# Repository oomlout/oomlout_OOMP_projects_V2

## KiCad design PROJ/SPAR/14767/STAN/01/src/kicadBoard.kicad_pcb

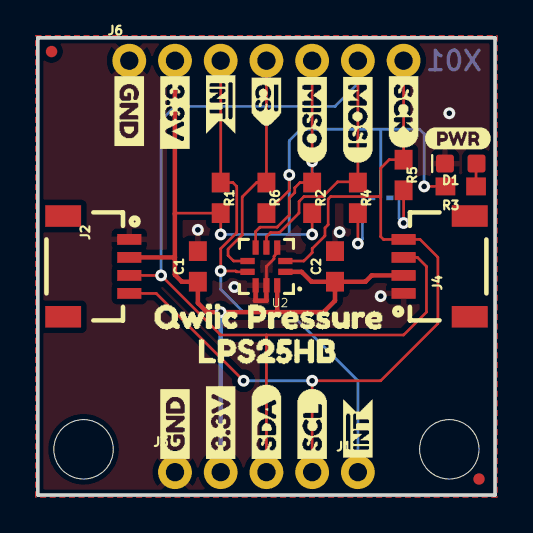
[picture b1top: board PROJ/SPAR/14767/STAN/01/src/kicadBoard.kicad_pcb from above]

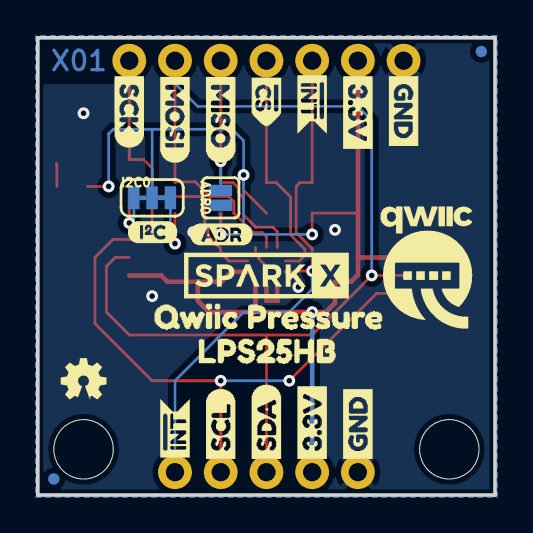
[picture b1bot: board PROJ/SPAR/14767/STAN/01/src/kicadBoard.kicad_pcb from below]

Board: 2 copper layers, 25.4 x 25.4 mm, 58 parts (23 on the bottom side), 10 nets.

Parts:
ADR0: SMT-JUMPER_2_NO_SILK
C1: 4.7uF; 0603
C2: 0.1uF; 0603
D1: RED; LED-0603
FRAME1: FRAME-LETTER; CREATIVE_COMMONS
I2C0: SMT-JUMPER_3_2-NC_TRACE_SILK
J1: 1X01_NO_SILK
J2, J4: 1X04_1MM_RA
J3: PTH; 1X04_NO_SILK
J6: 1X07_NO_SILK
JP1, JP2, JP5, JP6: FIDUCIALUFIDUCIAL; MICRO-FIDUCIAL
JP3, JP4: STAND-OFF
LOGO1: OSHW-LOGOMINI; OSHW-LOGO-MINI
R1, R2, R6: 10k; 0603
R3: 1k; 0603
R4, R5: 2.2k; 0603
U2: LPS25HB
U$1, U$37: QWIIC_PRESSURE1
U$2: SPARKX-LOGO4; SPARKX-MEDIUM
U$3, U$22, U$31, U$32: GND1
U$4, U$21, U$30, U$33: 3#3V2
U$5, U$27: SDA8
U$6, U$26: SCL9
U$7, U$35: LPS25HB0
U$9: QWIIC-LOGO-MEDIUM
U$10, U$11: MISO
U$12: I_SUPER2_C-()-03
U$15: PWR-()-03
U$16, U$17: MOSI
U$18, U$19: SCK-[)
U$20, U$23: CS#-[_
U$24, U$25, U$28, U$29: INT#-[_
U$34: ADR-()-03

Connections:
3.3V: C1.1, C2.1, I2C0.2, J2.2, J3.2, J4.2, J6.2, R1.2, R2.2, R3.2, R6.2, U2.1, U2.10
ADDR/MISO: ADR0.2, J6.5, R2.1, U2.5
CS: J6.4, R6.1, U2.6
GND: ADR0.1, C1.2, C2.2, D1.C, J2.1, J3.1, J4.1, J6.1, U2.3, U2.8, U2.9
unnamed: I2C0.1, R5.2
unnamed: I2C0.3, R4.2
unnamed: D1.A, R3.1
SCL/SCK: J2.4, J3.4, J4.4, J6.7, R5.1, U2.2
SDA/MOSI: J2.3, J3.3, J4.3, J6.6, R4.1, U2.4
~INT: J1.1, J6.3, R1.1, U2.7

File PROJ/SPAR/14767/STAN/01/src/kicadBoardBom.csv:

"Id";"Designator";"Package";"Quantity";"Designation";"Supplier and ref";
1;"U$28,U$24,U$25,U$29";"INT#-[_";4;"";;;
2;"C1";"0603";1;"4.7uF";;;
3;"U$37,U$1";"QWIIC_PRESSURE1";2;"";;;
4;"U$17,U$16";"MOSI";2;"";;;
5;"U$35,U$7";"LPS25HB0";2;"";;;
6;"U$31,U$22,U$32,U$3";"GND1";4;"";;;
7;"U$26,U$6";"SCL9";2;"";;;
8;"D1";"LED-0603";1;"RED";;;
9;"JP3,JP4";"STAND-OFF";2;"STAND-OFF";;;
10;"R3";"0603";1;"1k";;;
11;"JP2,JP6,JP1,JP5";"MICRO-FIDUCIAL";4;"FIDUCIALUFIDUCIAL";;;
12;"R1,R6,R2";"0603";3;"10k";;;
13;"R4,R5";"0603";2;"2.2k";;;
14;"U$18,U$19";"SCK-[)";2;"";;;
15;"J4,J2";"1X04_1MM_RA";2;"";;;
16;"U$10,U$11";"MISO";2;"";;;
17;"U$15";"PWR-()-03";1;"";;;
18;"C2";"0603";1;"0.1uF";;;
19;"U$30,U$21,U$4,U$33";"3#3V2";4;"";;;
20;"U$20,U$23";"CS#-[_";2;"";;;
21;"U$27,U$5";"SDA8";2;"";;;
22;"J6";"1X07_NO_SILK";1;"";;;
23;"U2";"LPS25HB";1;"LPS25HB";;;
24;"FRAME1";"CREATIVE_COMMONS";1;"FRAME-LETTER";;;
25;"J3";"1X04_NO_SILK";1;"PTH";;;
26;"J1";"1X01_NO_SILK";1;"";;;
27;"U$9";"QWIIC-LOGO-MEDIUM";1;"";;;
28;"U$34";"ADR-()-03";1;"";;;
29;"ADR0";"SMT-JUMPER_2_NO_SILK";1;"";;;
30;"I2C0";"SMT-JUMPER_3_2-NC_TRACE_SILK";1;"";;;
31;"U$12";"I_SUPER2_C-()-03";1;"";;;
32;"LOGO1";"OSHW-LOGO-MINI";1;"OSHW-LOGOMINI";;;
33;"U$2";"SPARKX-MEDIUM";1;"SPARKX-LOGO4";;;

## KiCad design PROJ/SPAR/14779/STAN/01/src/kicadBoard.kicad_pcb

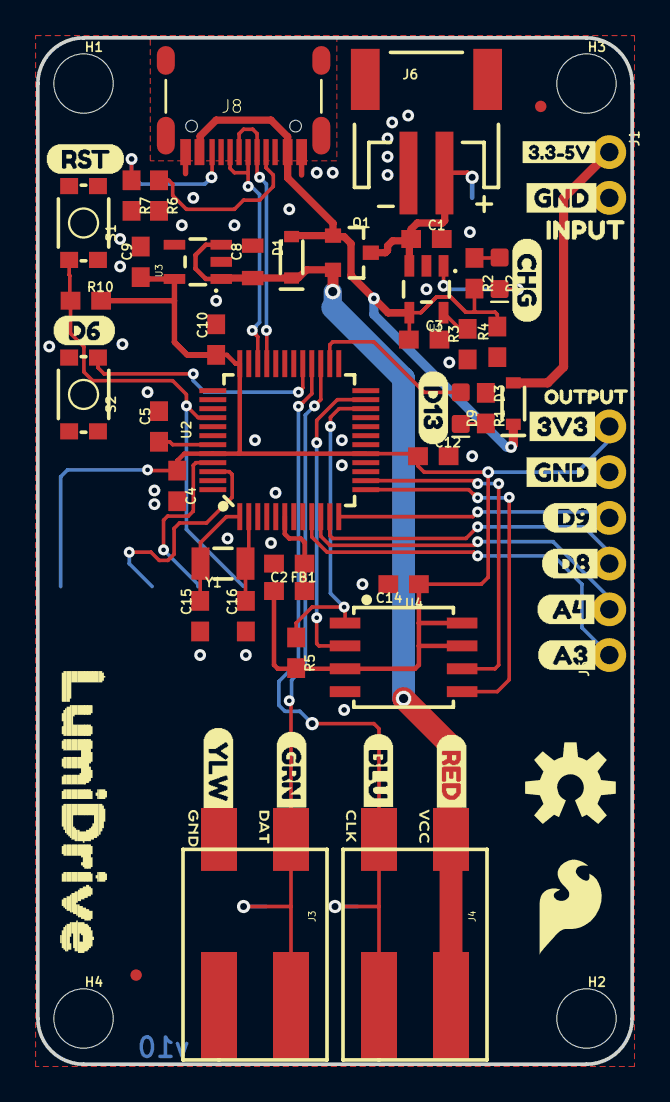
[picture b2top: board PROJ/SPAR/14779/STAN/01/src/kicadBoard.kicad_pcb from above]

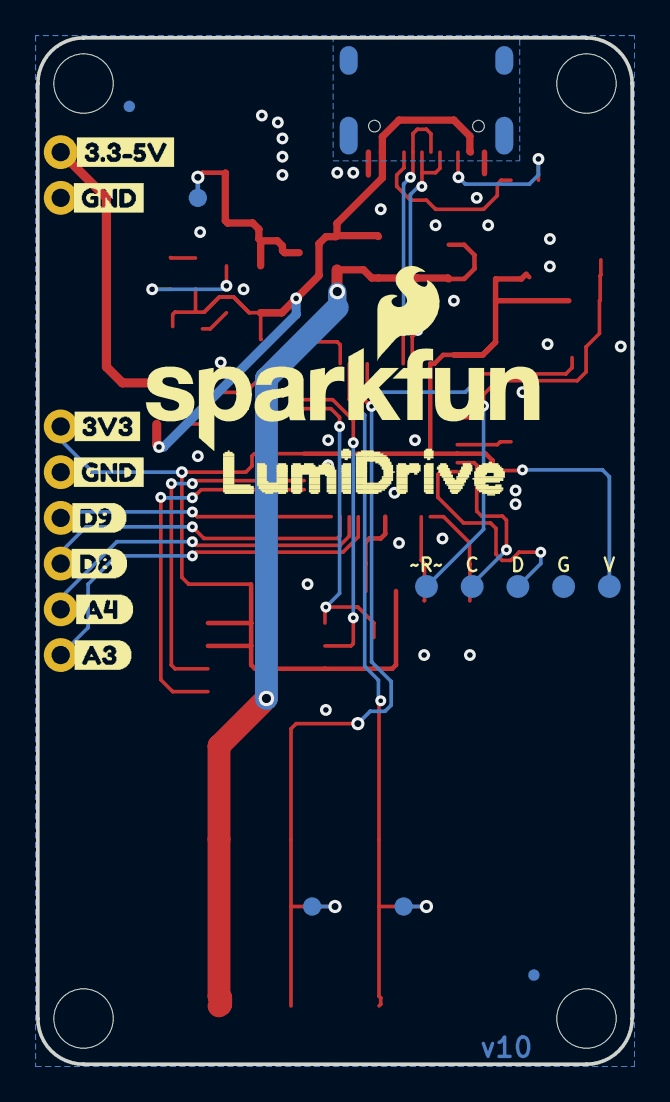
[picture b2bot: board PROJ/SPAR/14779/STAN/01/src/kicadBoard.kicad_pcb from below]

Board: 4 copper layers, 33.0 x 57.0 mm, 91 parts (20 on the bottom side), 34 nets.

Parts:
C1, C3: 4.7uF; 0603
C2, C4, C5, C10, C12, C14: 0.1uF; 0603
C8: 1.0uF; 0805
C9: 2.2uF; 0603
C15, C16: 15pF; 0603
D1, D3: 1A/23V/620mV; SOD-323
D2: Yellow; LED-0603
D9: BLUE; LED-0603
FB1: 30Ω/1.8A; 0603
FD1, FD2, FD3, FD4: FIDUCIALUFIDUCIAL; FIDUCIAL-MICRO
FRAME1: FRAME-LETTER; CREATIVE_COMMONS
H1, H2, H3, H4: STAND-OFF
J1: 1X02_NO_SILK
J3, J4: 1X02_POKEHOME
J5: 1X06_NO_SILK
J6: JST-2-SMD
J8: USB-C-16P
LOGO1: OSHW-LOGOM; OSHW-LOGO-M
LOGO3: SFE_LOGO_NAME_FLAME.2_INCH; SFE_LOGO_NAME_FLAME_.2
Q1: 2.5A/30V/105mΩ; SOT23-3
R1, R2: 1k; 0603
R3: 2.0k; 0603
R4, R5, R10: 10k; 0603
R6, R7: 5.1k; 0603
S1: RESET; TACTILE_SWITCH_SMD_4.6X2.8MM
S2: BTN2; TACTILE_SWITCH_SMD_4.6X2.8MM
TP1: TP-SWDIO; PAD.03X.05
TP2: TP-SWCLK; PAD.03X.05
TP3: TP-!RESET!; PAD.03X.05
TP4: TP-3.3V; PAD.03X.05
TP5: TP-GND; PAD.03X.05
TP6, TP7, TP8: TEST-POINT3X4; PAD.03X.04
U1: MCP73831; SOT23-5
U2: ATSAMD21G-A; TQFP-48
U3: 3.3V; SOT23-5
U4: W25Q32FV; SOIC-8
U$1, U$5, U$19, U$26: GND-04
U$2: GRN0
U$3: BLU0
U$4: YLW0
U$6, U$41: LUMIDRIVE0
U$8, U$29: 3#3#5V0
U$9: INPUT0
U$10: RED0
U$11: RST0
U$12: D60
U$13: CLK1
U$14: DAT2
U$15: GND0
U$16: VCC3
U$17: CHG0
U$18: D130
U$20, U$27: 3V3-04
U$21, U$40: D90
U$22, U$39: D80
U$23, U$38: A40
U$24, U$37: A30
U$25: OUTPUT0
U$28: SFE_LOGO_FLAME_.2
Y1: 32.768kHz; CRYSTAL-SMD-3.2X1.5MM

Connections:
3.3V: C4.1, C9.1, C10.1, C12.1, C14.1, FB1.1, J5.6, R5.2, R10.2, TP4.P$1, U2.17, U2.36, U2.44, U3.5, U4.3, U4.7, U4.8
5V: D3.A, J1.1
A3: J5.1, U2.9
A4: J5.2, U2.10
D6_BTN: S2.4, U2.29
D8: J5.3, U2.11
D9: J5.4, U2.12
D13_LED1: D9.A, U2.26
FLASH_CS: R5.1, U2.22, U4.1
GND: C1.2, C2.2, C3.2, C4.2, C5.2, C8.2, C9.2, C10.2, C12.2, C14.2, C15.1, C16.1, J1.2, J3.P1, J3.P3, J5.5, J6.1, J8.GND, J8.GND2, R1.1, R3.1, R4.1, R6.2, R7.2, S1.3, S2.1, TP5.P$1, U1.2, U2.5, U2.18, U2.35, U2.42, U3.2, U4.4
LED_MOSI: J3.P2, J3.P4, TP7.P$1, U2.27
LED_SCK: J4.P1, J4.P3, TP8.P$1, U2.28
unnamed: D9.C, R1.2
unnamed: C15.2, U2.1, Y1.P$2
unnamed: C16.2, U2.2, Y1.P$1
unnamed: D2.A, R2.1
unnamed: J8.B5, R7.1
unnamed: J8.A5, R6.1
unnamed: D2.C, U1.1
unnamed: R3.2, U1.5
SHIELD: J8.SHLD1, J8.SHLD2, J8.SHLD3, J8.SHLD4, J8.SHLD5, J8.SHLD6, J8.SHLD7, J8.SHLD8
SPI_MISO: U2.23, U4.2
SPI_MOSI: U2.13, U4.5
SPI_SCK: U2.14, U4.6
SWCLK: TP2.P$1, U2.45
SWDIO: TP1.P$1, U2.46
USB_D+: J8.A6, J8.B6, U2.34
USB_D-: J8.A7, J8.B7, U2.33
VDDANA: C2.1, FB1.2, U2.6
VDDCORE: C5.1, U2.43
VIN: C8.1, D1.C, J4.P2, J4.P4, Q1.2, U3.1, U3.3
V_BATT: C1.1, J6.2, Q1.3, TP6.P$1, U1.3
V_USB: C3.1, D1.A, D3.C, J8.VBUS1, J8.VBUS2, Q1.1, R2.2, R4.2, U1.4
~RESET: R10.1, S1.2, TP3.P$1, U2.40

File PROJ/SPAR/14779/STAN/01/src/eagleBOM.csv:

"Part";"Value";"Device";"Package";"Description";"DESIGNER";"PROD_ID";"REV";"SF_ID";"VALUE";
"C1";"4.7uF";"4.7UF-0603-6.3V-(10%)";"0603";"4.7µF ceramic capacitors";"";"CAP-08280";"";"";"4.7uF";
"C2";"0.1uF";"0.1UF-0603-25V-(+80/-20%)";"0603";"0.1µF ceramic capacitors";"";"CAP-00810";"";"";"0.1uF";
"C3";"4.7uF";"4.7UF-0603-6.3V-(10%)";"0603";"4.7µF ceramic capacitors";"";"CAP-08280";"";"";"4.7uF";
"C4";"0.1uF";"0.1UF-0603-25V-(+80/-20%)";"0603";"0.1µF ceramic capacitors";"";"CAP-00810";"";"";"0.1uF";
"C5";"0.1uF";"0.1UF-0603-25V-(+80/-20%)";"0603";"0.1µF ceramic capacitors";"";"CAP-00810";"";"";"0.1uF";
"C8";"1.0uF";"1.0UF-0805-25V-10%";"0805";"1µF ceramic capacitors";"";"CAP-08064";"";"";"1.0uF";
"C9";"2.2uF";"2.2UF-0603-10V-20%";"0603";"2.2µF ceramic capacitors";"";"CAP-07888";"";"";"2.2uF";
"C10";"0.1uF";"0.1UF-0603-25V-(+80/-20%)";"0603";"0.1µF ceramic capacitors";"";"CAP-00810";"";"";"0.1uF";
"C12";"0.1uF";"0.1UF-0603-25V-(+80/-20%)";"0603";"0.1µF ceramic capacitors";"";"CAP-00810";"";"";"0.1uF";
"C14";"0.1uF";"0.1UF-0603-25V-(+80/-20%)";"0603";"0.1µF ceramic capacitors";"";"CAP-00810";"";"";"0.1uF";
"C15";"15pF";"15PF-0603-50V-5%";"0603";"15pF ceramic capacitors";"";"CAP-07881";"";"";"15pF";
"C16";"15pF";"15PF-0603-50V-5%";"0603";"15pF ceramic capacitors";"";"CAP-07881";"";"";"15pF";
"D1";"1A/23V/620mV";"DIODE-SCHOTTKY-BAT20J";"SOD-323";"Schottky diode";"";"DIO-11623";"";"";"1A/23V/620mV";
"D2";"Yellow";"LED-YELLOW0603";"LED-0603";"Yellow SMD LED";"";"DIO-09003";"";"";"Yellow";
"D3";"1A/23V/620mV";"DIODE-SCHOTTKY-BAT20J";"SOD-323";"Schottky diode";"";"DIO-11623";"";"";"1A/23V/620mV";
"D9";"BLUE";"LED-BLUE0603";"LED-0603";"Blue SMD LED";"";"DIO-08575";"";"";"BLUE";
"FB1";"30Ω/1.8A";"INDUCTORFB-30OHM";"0603";"Inductors";"";"NDUC-07859";"";"";"";
"FD1";"FIDUCIALUFIDUCIAL";"FIDUCIALUFIDUCIAL";"FIDUCIAL-MICRO";"Fiducial Alignment Points";"";"";"";"";"";
"FD2";"FIDUCIALUFIDUCIAL";"FIDUCIALUFIDUCIAL";"FIDUCIAL-MICRO";"Fiducial Alignment Points";"";"";"";"";"";
"FD3";"FIDUCIALUFIDUCIAL";"FIDUCIALUFIDUCIAL";"FIDUCIAL-MICRO";"Fiducial Alignment Points";"";"";"";"";"";
"FD4";"FIDUCIALUFIDUCIAL";"FIDUCIALUFIDUCIAL";"FIDUCIAL-MICRO";"Fiducial Alignment Points";"";"";"";"";"";
"FRAME1";"FRAME-LETTER";"FRAME-LETTER";"CREATIVE_COMMONS";"Schematic Frame - Letter";"";"";"";"";"";
"H1";"STAND-OFF";"STAND-OFF";"STAND-OFF";"Stand Off";"";"";"";"";"";
"H2";"STAND-OFF";"STAND-OFF";"STAND-OFF";"Stand Off";"";"";"";"";"";
"H3";"STAND-OFF";"STAND-OFF";"STAND-OFF";"Stand Off";"";"";"";"";"";
"H4";"STAND-OFF";"STAND-OFF";"STAND-OFF";"Stand Off";"";"";"";"";"";
"J1";"";"CONN_021X02_NO_SILK";"1X02_NO_SILK";"Multi connection point. Often used as Generic Header-pin footprint for 0.1 inch spaced/style header connections";"";"";"";"";"";
"J3";"";"CONN_02SMALL_POKEHOME";"1X02_POKEHOME";"Multi connection point. Often used as Generic Header-pin footprint for 0.1 inch spaced/style header connections";"";"CONN-13512";"";"";"";
"J4";"";"CONN_02SMALL_POKEHOME";"1X02_POKEHOME";"Multi connection point. Often used as Generic Header-pin footprint for 0.1 inch spaced/style header connections";"";"CONN-13512";"";"";"";
"J5";"";"CONN_06NO_SILK_FEMALE_PTH";"1X06_NO_SILK";"Multi connection point. Often used as Generic Header-pin footprint for 0.1 inch spaced/style header connections";"";"CONN-08437";"";"";"";
"J6";"";"JST_2MM_MALE";"JST-2-SMD";"JST 2MM MALE RA CONNECTOR";"";"CONN-11443";"";"PRT-08612";"";
"J8";"";"USB_C16PIN";"USB-C-16P";"USB Type C 16Pin Connector";"";"CONN-14122";"";"";"";
"LOGO1";"OSHW-LOGOM";"OSHW-LOGOM";"OSHW-LOGO-M";"Open-Source Hardware (OSHW) Logo";"";"";"";"";"";
"LOGO3";"SFE_LOGO_NAME_FLAME.2_INCH";"SFE_LOGO_NAME_FLAME.2_INCH";"SFE_LOGO_NAME_FLAME_.2";"SparkFun Font Logo w/ Flame";"";"";"";"";"";
"Q1";"2.5A/30V/105mΩ";"MOSFET_PCH-DMG2307L";"SOT23-3";"P-channel MOSFETs";"";"TRANS-11308";"";"";"2.5A/30V/105mΩ";
"R1";"1k";"1KOHM-0603-1/10W-1%";"0603";"1kΩ resistor";"";"RES-07856";"";"";"1k";
"R2";"1k";"1KOHM-0603-1/10W-1%";"0603";"1kΩ resistor";"";"RES-07856";"";"";"1k";
"R3";"2.0k";"2.0KOHM-0603-1/10W-5%";"0603";"2kΩ resistor";"";"RES-08296";"";"";"2.0k";
"R4";"10k";"10KOHM-0603-1/10W-1%";"0603";"10kΩ resistor";"";"RES-00824";"";"";"10k";
"R5";"10k";"10KOHM-0603-1/10W-1%";"0603";"10kΩ resistor";"";"RES-00824";"";"";"10k";
"R6";"5.1k";"5.1KOHM5.1KOHM-0603-1/10W-1%";"0603";"";"";"RES-12083";"";"";"5.1k";
"R7";"5.1k";"5.1KOHM5.1KOHM-0603-1/10W-1%";"0603";"";"";"RES-12083";"";"";"5.1k";
"R10";"10k";"10KOHM-0603-1/10W-1%";"0603";"10kΩ resistor";"";"RES-00824";"";"";"10k";
"S1";"RESET";"MOMENTARY-SWITCH-SPST-2-SMD-4.6X2.8MM";"TACTILE_SWITCH_SMD_4.6X2.8MM";"Momentary Switch (Pushbutton) - SPST - Two Circuits";"";"SWCH-13065";"";"";"";
"S2";"BTN2";"MOMENTARY-SWITCH-SPST-2-SMD-4.6X2.8MM";"TACTILE_SWITCH_SMD_4.6X2.8MM";"Momentary Switch (Pushbutton) - SPST - Two Circuits";"";"SWCH-13065";"";"";"";
"TP1";"TP-SWDIO";"TEST-POINT3X5";"PAD.03X.05";"SparkFun Test Points";"";"";"";"";"";
"TP2";"TP-SWCLK";"TEST-POINT3X5";"PAD.03X.05";"SparkFun Test Points";"";"";"";"";"";
"TP3";"TP-!RESET!";"TEST-POINT3X5";"PAD.03X.05";"SparkFun Test Points";"";"";"";"";"";
"TP4";"TP-3.3V";"TEST-POINT3X5";"PAD.03X.05";"SparkFun Test Points";"";"";"";"";"";
"TP5";"TP-GND";"TEST-POINT3X5";"PAD.03X.05";"SparkFun Test Points";"";"";"";"";"";
"TP6";"TEST-POINT3X4";"TEST-POINT3X4";"PAD.03X.04";"SparkFun Test Points";"";"";"";"";"";
"TP7";"TEST-POINT3X4";"TEST-POINT3X4";"PAD.03X.04";"SparkFun Test Points";"";"";"";"";"";
"TP8";"TEST-POINT3X4";"TEST-POINT3X4";"PAD.03X.04";"SparkFun Test Points";"";"";"";"";"";
"U1";"MCP73831";"MCP73831";"SOT23-5";"MCP73831T Li-Ion, Li-Pol Controller";"";"IC-09995";"";"";"";
"U2";"ATSAMD21G-A";"ATSAMD21G-A";"TQFP-48";"Atmel SAMD21G SMART ARM-Based Microcontroller";"";"IC-13064";"";"";"";
"U3";"3.3V";"V_REG_AP2112K-3.3V";"SOT23-5";"AP2112 - 600mA CMOS LDO Regulator w/ Enable";"";"VREG-12457";"";"";"3.3V";
"U4";"W25Q32FV";"W25Q32FVSS";"SOIC-8";"W25Q32FV 32Mb (4MB) Serial Flash Memory";"";"IC-13229";"";"";"W25Q32FV";
"Y1";"32.768kHz";"CRYSTAL-32.768KHZSMD-3.2X1.5";"CRYSTAL-SMD-3.2X1.5MM";"32.768kHz Crystal";"";"XTAL-13062";"";"";"32.768kHz";

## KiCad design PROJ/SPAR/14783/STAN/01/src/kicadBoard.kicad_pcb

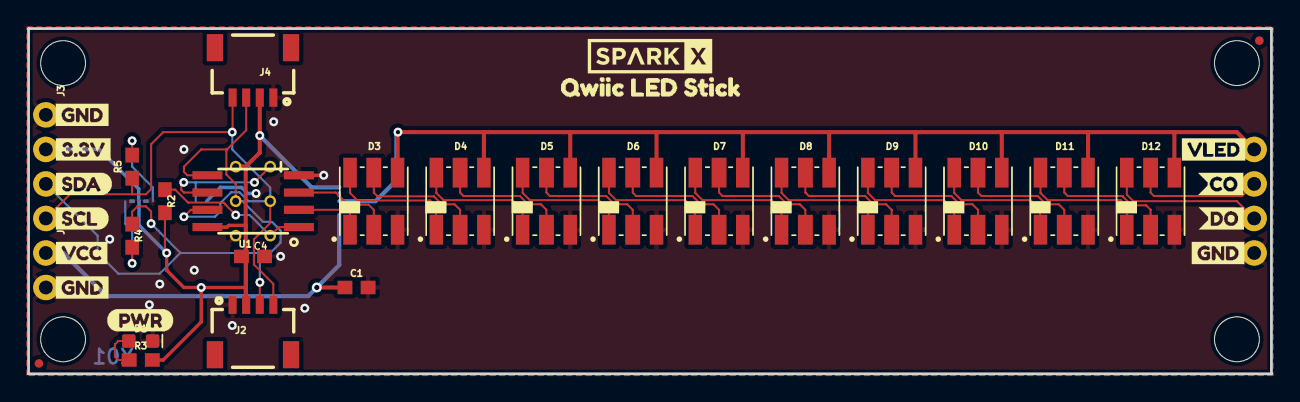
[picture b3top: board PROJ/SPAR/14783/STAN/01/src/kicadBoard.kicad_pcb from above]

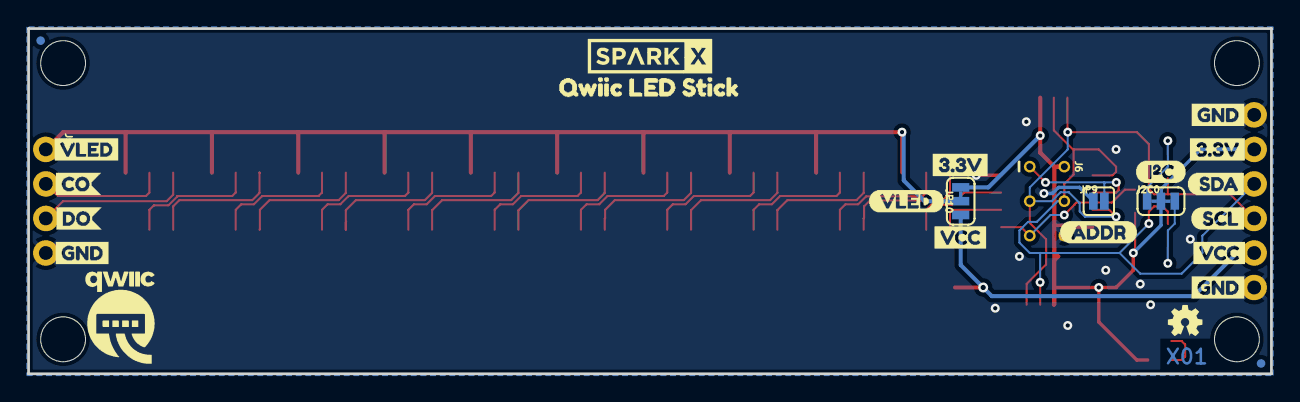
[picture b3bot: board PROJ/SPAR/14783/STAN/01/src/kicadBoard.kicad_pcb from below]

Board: 2 copper layers, 91.4 x 25.4 mm, 68 parts (26 on the bottom side), 33 nets.

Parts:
C1: 4.7uF; 0603
C4: 0.1uF; 0603
D1: RED; LED-0603
D3, D4, D5, D6, D7, D8, D9, D10, D11, D12: APA1025050; APA102-5050
FRAME1: FRAME-LETTER; CREATIVE_COMMONS
I2C0: SMT-JUMPER_3_2-NC_TRACE_SILK
J1: 1X02_NO_SILK
J2, J4: SMD; 1X04_1MM_RA
J3: PTH; 1X04_NO_SILK
J5: 1X04_NO_SILK
J6: AVR_SPI_PROG_3X2TESTPOINTS; 2X3_TEST_POINTS
JP1, JP2, JP5, JP6: FIDUCIALUFIDUCIAL; MICRO-FIDUCIAL
JP3, JP4, JP7, JP8: STAND-OFF
JP9: JUMPER-SMT_2_NO_SILK; SMT-JUMPER_2_NO_SILK
JP10: SMT-JUMPER_3_1-NC_TRACE_SILK
LOGO1: OSHW-LOGOMINI; OSHW-LOGO-MINI
R2: 4.7k; 0603
R3: 1k; 0603
R4, R5: 2.2k; 0603
U1: Tiny85-20-SMT; SO08-EIAJ_MCU
U$1, U$2: SPARKX-LOGO4; SPARKX-MEDIUM
U$3, U$8, U$12, U$22: GND1
U$4, U$21: 3#3V2
U$5, U$9: VLED4
U$6: DO8
U$7: CO5
U$10: (PWR)
U$11: (I_SUPER2_C)
U$13, U$32: QWIIC_LED_STICK1
U$15: DO12
U$16: CO9
U$17: SDA0
U$18: SCL1
U$19, U$20, U$31: VCC1
U$23, U$24: GND0
U$25: VLED3
U$26: SCL9
U$27: SDA8
U$28: ADDR2
U$29: QWIIC-LOGO-MEDIUM
U$30: 3#3V3

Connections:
3.3V: C4.1, I2C0.2, J2.2, J3.2, J4.2, J6.2, JP10.3, R2.2, R3.2, U1.8
ADDR(MISO): J6.1, JP9.2, U1.6
CLK: D3.P2, U1.3
CO(10): D12.P5, J5.2
DO: D3.P1, U1.2
DO(10): D12.P6, J5.3
GND: C1.2, C4.2, D1.C, D3.P3, D4.P3, D5.P3, D6.P3, D7.P3, D8.P3, D9.P3, D10.P3, D11.P3, D12.P3, J1.2, J2.1, J3.1, J4.1, J5.4, J6.6, JP9.1, U1.4
unnamed: I2C0.1, R5.2
unnamed: I2C0.3, R4.2
unnamed: D1.A, R3.1
unnamed: D11.P6, D12.P1
unnamed: D11.P5, D12.P2
unnamed: D10.P5, D11.P2
unnamed: D10.P6, D11.P1
unnamed: D9.P5, D10.P2
unnamed: D9.P6, D10.P1
unnamed: D8.P5, D9.P2
unnamed: D8.P6, D9.P1
unnamed: D7.P5, D8.P2
unnamed: D7.P6, D8.P1
unnamed: D6.P5, D7.P2
unnamed: D6.P6, D7.P1
unnamed: D5.P6, D6.P1
unnamed: D5.P5, D6.P2
unnamed: D4.P6, D5.P1
unnamed: D4.P5, D5.P2
unnamed: D3.P5, D4.P2
unnamed: D3.P6, D4.P1
SCL: J2.4, J3.4, J4.4, J6.3, R5.1, U1.7
SDA: J2.3, J3.3, J4.3, J6.4, R4.1, U1.5
VCC: C1.1, J1.1, JP10.1
VLED: D3.P4, D4.P4, D5.P4, D6.P4, D7.P4, D8.P4, D9.P4, D10.P4, D11.P4, D12.P4, J5.1, JP10.2
~RST: J6.5, R2.1, U1.1

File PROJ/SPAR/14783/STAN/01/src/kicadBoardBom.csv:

"Id";"Designator";"Package";"Quantity";"Designation";"Supplier and ref";
1;"R5,R4";"0603";2;"2.2k";;;
2;"R3";"0603";1;"1k";;;
3;"U$21,U$4";"3#3V2";2;"";;;
4;"JP8,JP4,JP7,JP3";"STAND-OFF";4;"STAND-OFF";;;
5;"U$10";"(PWR)";1;"";;;
6;"D11,D10,D3,D7,D6,D8,D9,D12,D4,D5";"APA102-5050";10;"APA1025050";;;
7;"R2";"0603";1;"4.7k";;;
8;"JP6,JP2,JP1,JP5";"MICRO-FIDUCIAL";4;"FIDUCIALUFIDUCIAL";;;
9;"U$9,U$5";"VLED4";2;"";;;
10;"U$22,U$12,U$8,U$3";"GND1";4;"";;;
11;"J2,J4";"1X04_1MM_RA";2;"SMD";;;
12;"C4";"0603";1;"0.1uF";;;
13;"U$1,U$2";"SPARKX-MEDIUM";2;"SPARKX-LOGO4";;;
14;"U$24,U$23";"GND0";2;"";;;
15;"FRAME1";"CREATIVE_COMMONS";1;"FRAME-LETTER";;;
16;"C1";"0603";1;"4.7uF";;;
17;"U$15";"DO12";1;"";;;
18;"U$32,U$13";"QWIIC_LED_STICK1";2;"";;;
19;"U$26";"SCL9";1;"";;;
20;"U$19,U$31,U$20";"VCC1";3;"";;;
21;"J1";"1X02_NO_SILK";1;"";;;
22;"U1";"SO08-EIAJ_MCU";1;"Tiny85-20-SMT";;;
23;"D1";"LED-0603";1;"RED";;;
24;"U$27";"SDA8";1;"";;;
25;"J3";"1X04_NO_SILK";1;"PTH";;;
26;"U$16";"CO9";1;"";;;
27;"U$25";"VLED3";1;"";;;
28;"U$17";"SDA0";1;"";;;
29;"U$7";"CO5";1;"";;;
30;"I2C0";"SMT-JUMPER_3_2-NC_TRACE_SILK";1;"";;;
31;"U$6";"DO8";1;"";;;
32;"U$30";"3#3V3";1;"";;;
33;"U$18";"SCL1";1;"";;;
34;"LOGO1";"OSHW-LOGO-MINI";1;"OSHW-LOGOMINI";;;
35;"JP9";"SMT-JUMPER_2_NO_SILK";1;"JUMPER-SMT_2_NO_SILK";;;
36;"U$28";"ADDR2";1;"";;;
37;"U$11";"(I_SUPER2_C)";1;"";;;
38;"JP10";"SMT-JUMPER_3_1-NC_TRACE_SILK";1;"";;;
39;"U$29";"QWIIC-LOGO-MEDIUM";1;"";;;
40;"J5";"1X04_NO_SILK";1;"";;;
41;"J6";"2X3_TEST_POINTS";1;"AVR_SPI_PROG_3X2TESTPOINTS";;;

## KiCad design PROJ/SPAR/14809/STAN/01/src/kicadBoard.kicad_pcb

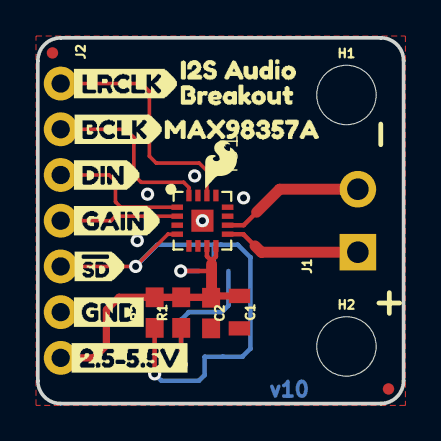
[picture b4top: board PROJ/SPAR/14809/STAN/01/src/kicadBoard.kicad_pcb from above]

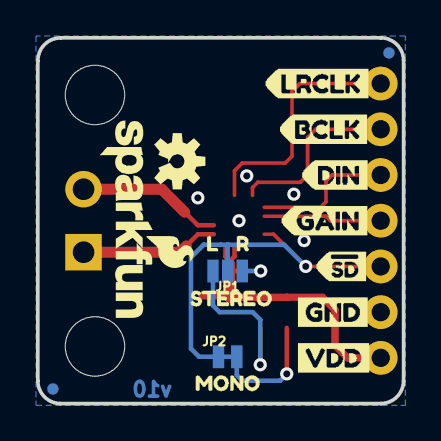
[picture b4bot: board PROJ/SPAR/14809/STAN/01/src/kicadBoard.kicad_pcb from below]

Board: 2 copper layers, 20.3 x 20.3 mm, 40 parts (17 on the bottom side), 11 nets.

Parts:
C1: 10uF; 0805
C2: 0.1uF; 0603
FD1, FD2, FD3, FD4: FIDUCIALUFIDUCIAL; FIDUCIAL-MICRO
FRAME1: FRAME-LETTER; CREATIVE_COMMONS
H1, H2: STAND-OFF
IC1: MAX98357A; TQFN-16
J1: SCREWTERMINAL-3.5MM-2-NS
J2: 1X07_NO_SILK
JP1: SMT-JUMPER_3_NO_NO-SILK
JP2: SMT-JUMPER_2_NC_TRACE_NO-SILK
LOGO1: SFE_LOGO_NAME_FLAME.1_INCH; SFE_LOGO_NAME_FLAME_.1
LOGO2: OSHW-LOGOS; OSHW-LOGO-S
R1: 300k; 0603
R2: 1M; 0603
U$1: 2#5#5#5V13
U$2, U$23: GND9
U$3: #SD7
U$4: GAIN6
U$5: DIN5
U$6: BCLK4
U$7: LRCLK3
U$8: I2S_AUDIO0
U$9: BREAKOUT1
U$10: MAX98357A2
U$11: LRCLK0
U$12: BCLK1
U$13: DIN2
U$14: GAIN3
U$15: SFE_LOGO_FLAME_.1
U$16: MONO12
U$17: L10
U$18: R11
U$19: STEREO14
U$20: #SD4
U$22: VDD8

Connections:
BCLK: IC1.P$16, J2.2
DIN: IC1.P$1, J2.3
GAIN: IC1.P$2, J2.4
GND: C1.2, C2.2, IC1.P$3, IC1.P$11, IC1.P$15, IC1.P$EP, J2.6
LRCLK: IC1.P$14, J2.1
unnamed: JP2.2, R2.1
unnamed: JP1.3, R1.1
OUT+: IC1.P$9, J1.1
OUT-: IC1.P$10, J1.2
VDD: C1.1, C2.1, IC1.P$7, IC1.P$8, J2.7, JP1.1, R1.2, R2.2
~SD: IC1.P$4, J2.5, JP1.2, JP2.1

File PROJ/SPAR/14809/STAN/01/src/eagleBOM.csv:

"Part";"Value";"Device";"Package";"Description";"PROD_ID";"VALUE";
"C1";"10uF";"10UF-0805-10V-10%";"0805";"10.0µF ceramic capacitors";"CAP-11330";"10uF";
"C2";"0.1uF";"0.1UF-0603-25V-(+80/-20%)";"0603";"0.1µF ceramic capacitors";"CAP-00810";"0.1uF";
"FD1";"FIDUCIALUFIDUCIAL";"FIDUCIALUFIDUCIAL";"FIDUCIAL-MICRO";"Fiducial Alignment Points";"";"";
"FD2";"FIDUCIALUFIDUCIAL";"FIDUCIALUFIDUCIAL";"FIDUCIAL-MICRO";"Fiducial Alignment Points";"";"";
"FD3";"FIDUCIALUFIDUCIAL";"FIDUCIALUFIDUCIAL";"FIDUCIAL-MICRO";"Fiducial Alignment Points";"";"";
"FD4";"FIDUCIALUFIDUCIAL";"FIDUCIALUFIDUCIAL";"FIDUCIAL-MICRO";"Fiducial Alignment Points";"";"";
"FRAME1";"FRAME-LETTER";"FRAME-LETTER";"CREATIVE_COMMONS";"Schematic Frame - Letter";"";"";
"H1";"STAND-OFF";"STAND-OFF";"STAND-OFF";"Stand Off";"";"";
"H2";"STAND-OFF";"STAND-OFF";"STAND-OFF";"Stand Off";"";"";
"IC1";"MAX98357A";"MAX98357A";"TQFN-16";"I2S DAC 3.2W (4-8ohm)";"IC-14032";"MAX98357A";
"J1";"";"CONN_023.5MM-NO_SILK";"SCREWTERMINAL-3.5MM-2-NS";"Multi connection point. Often used as Generic Header-pin footprint for 0.1 inch spaced/style header connections";"CONN-08399";"";
"J2";"";"CONN_07NO_SILK";"1X07_NO_SILK";"Multi connection point. Often used as Generic Header-pin footprint for 0.1 inch spaced/style header connections";"";"";
"JP1";"";"JUMPER-SMT_3_NO_NO-SILK";"SMT-JUMPER_3_NO_NO-SILK";"Normally open jumper";"";"";
"JP2";"";"JUMPER-SMT_2_NC_TRACE_NO-SILK";"SMT-JUMPER_2_NC_TRACE_NO-SILK";"Normally closed trace jumper";"";"";
"LOGO1";"SFE_LOGO_NAME_FLAME.1_INCH";"SFE_LOGO_NAME_FLAME.1_INCH";"SFE_LOGO_NAME_FLAME_.1";"SparkFun Font Logo w/ Flame";"";"";
"LOGO2";"OSHW-LOGOS";"OSHW-LOGOS";"OSHW-LOGO-S";"Open-Source Hardware (OSHW) Logo";"";"";
"R1";"300k";"300KOHM-0603-1/10W-1%";"0603";"300kΩ resistor";"RES-10809";"300k";
"R2";"1M";"1MOHM-0603-1/4W-5%";"0603";"1MΩ resistor";"RES-07868";"1M";

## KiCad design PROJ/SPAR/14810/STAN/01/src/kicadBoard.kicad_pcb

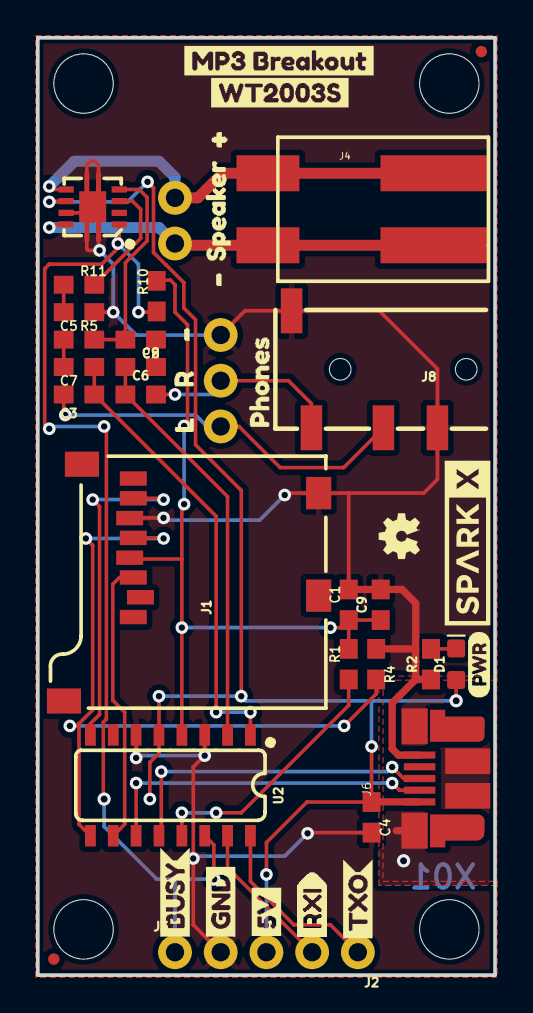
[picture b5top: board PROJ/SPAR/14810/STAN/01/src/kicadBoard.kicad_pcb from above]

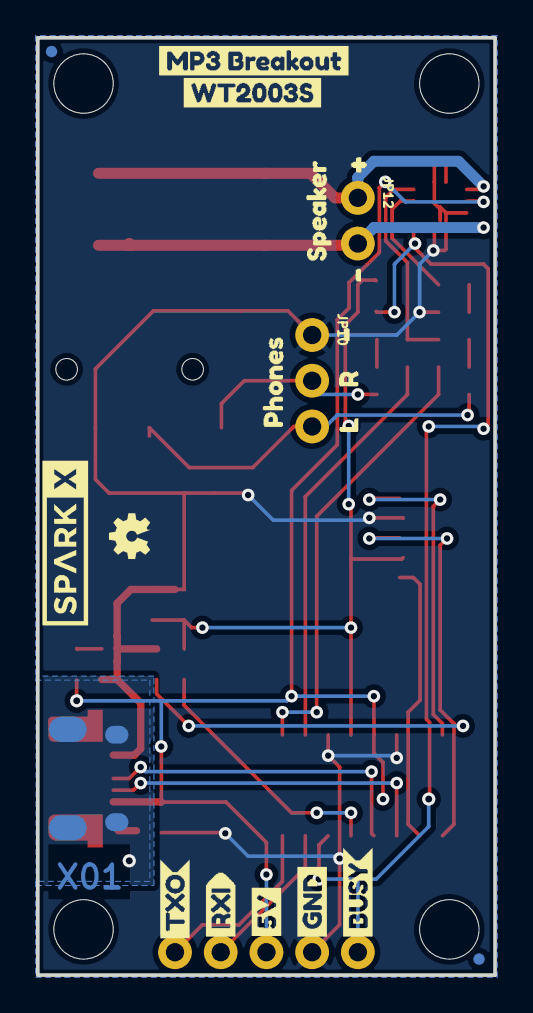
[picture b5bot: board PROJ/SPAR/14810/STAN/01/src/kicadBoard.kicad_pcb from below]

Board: 2 copper layers, 25.4 x 52.1 mm, 69 parts (20 on the bottom side), 25 nets.

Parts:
C1: 10uF; 0603
C3, C6: 0.22uF; 0603
C4, C5, C9: 1.0uF; 0603
C7, C8: 0.1uF; 0603
D1: RED; LED-0603
FRAME1: FRAME-LETTER; CREATIVE_COMMONS
J1: MICRO-SD; MICRO-SD-SOCKET
J2: Header; 1X04_NO_SILK
J3: 1X01_NO_SILK
J4: Poke-Home; 1X02_POKEHOME
J6: USB-MICROB-PTH-MILL
J8: 3.5mm Audio; AUDIO_JACK_3.5MM_TRRS_SMD_RA
JP1, JP2, JP5, JP6: FIDUCIALUFIDUCIAL; MICRO-FIDUCIAL
JP3, JP4, JP11, JP13: STAND-OFF
JP10: PTH; 1X03_NO_SILK
JP12: PTH; 1X02_NO_SILK
LOGO1: OSHW-LOGOMINI; OSHW-LOGO-MINI
LOGO2: OSHW-LOGOMINI; OSHW-LOGO-MINI@1
R1, R5, R9, R10: 10k; 0603
R2: 1k; 0603
R4: 2.2k; 0603
R11: 4.7k; 0603
U1: TPA2005D1; QFN-8_PAD
U2: WT2003S; SO16
U$1, U$22: GND1
U$2, U$11: SPARKX-LOGO4; SPARKX-MEDIUM
U$3, U$41: L12
U$4, U$39: R11
U$6, U$9: TXO0
U$7, U$8, U$23: RXI0
U$10, U$15, U$21, U$25: #6
U$12, U$24: MP3_BREAKOUT0
U$13, U$14: BUSY0
U$16, U$40: PHONES0
U$17: PWR-()-03
U$18, U$20: SPEAKER1
U$19, U$28: #5
U$26, U$27: WT2003S0
U$29, U$30: 5V0

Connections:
5V: C4.1, D1.A, J2.3, J6.VBUS, U1.6, U2.5
AC-L: C3.2, J8.RING1, JP10.3
AC-R: C6.2, J8.TIP, JP10.2
ADKEY: R1.1, U2.13
D+: J6.D+, U2.12
D-: J6.D-, U2.11
GND: C1.2, C4.2, C5.1, C9.2, J1.CD1, J1.GND, J2.4, J6.GND, J8.EARTH, J8.RING2, JP10.1, R2.1, R4.1, U1.7, U1.9, U1.10, U1.11, U1.12, U1.13, U2.3, U2.6
IN+AMP: R11.2, U1.3
IN-AMP: R5.2, R9.2, U1.4
MP3-RXI: J2.2, U2.15
MP3-TXO: J2.1, U2.16
unnamed: D1.C, R2.2
unnamed: C8.2, R9.1
unnamed: C5.2, R11.1
unnamed: C7.2, R5.1
OUT+: J4.P2, J4.P4, JP12.1, U1.5
OUT-: J4.P1, J4.P3, JP12.2, U1.8
SD_CLK: J1.SCLK, R4.2, U2.9
SD_CMD: J1.DI, U2.10
SD_DAT: J1.DO, U2.8
SHLD: J6.SHIELD, J6.SHIELD2, J6.SHIELD3, J6.SHIELD4, J6.SHIELD5, J6.SHIELD6, J6.SHIELD7, J6.SHIELD8, J6.SHIELD9, J6.SHIELD10
VCCIO: C1.1, C9.1, J1.VCC, R1.2, R10.2, U2.4
VOUTL: C3.1, C7.1, U2.1
VOUTR: C6.1, C8.1, U2.2
~SDN: J3.1, R10.1, U1.1, U2.14

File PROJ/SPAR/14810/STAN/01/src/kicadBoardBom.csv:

"Id";"Designator";"Package";"Quantity";"Designation";"Supplier and ref";
1;"U$41,U$3";"L12";2;"";;;
2;"C8,C7";"0603";2;"0.1uF";;;
3;"J2";"1X04_NO_SILK";1;"Header";;;
4;"JP4,JP11,JP13,JP3";"STAND-OFF";4;"STAND-OFF";;;
5;"U$20,U$18";"SPEAKER1";2;"";;;
6;"U$10,U$25,U$21,U$15";"#6";4;"";;;
7;"R5,R10,R9,R1";"0603";4;"10k";;;
8;"J4";"1X02_POKEHOME";1;"Poke-Home";;;
9;"J3";"1X01_NO_SILK";1;"";;;
10;"FRAME1";"CREATIVE_COMMONS";1;"FRAME-LETTER";;;
11;"U$12,U$24";"MP3_BREAKOUT0";2;"";;;
12;"J8";"AUDIO_JACK_3.5MM_TRRS_SMD_RA";1;"3.5mm Audio";;;
13;"U$29,U$30";"5V0";2;"";;;
14;"U$23,U$7,U$8";"RXI0";3;"";;;
15;"R4";"0603";1;"2.2k";;;
16;"U$13,U$14";"BUSY0";2;"";;;
17;"D1";"LED-0603";1;"RED";;;
18;"U$26,U$27";"WT2003S0";2;"";;;
19;"C5,C4,C9";"0603";3;"1.0uF";;;
20;"U2";"SO16";1;"WT2003S";;;
21;"R2";"0603";1;"1k";;;
22;"C6,C3";"0603";2;"0.22uF";;;
23;"U1";"QFN-8_PAD";1;"TPA2005D1";;;
24;"U$6,U$9";"TXO0";2;"";;;
25;"U$39,U$4";"R11";2;"";;;
26;"U$2,U$11";"SPARKX-MEDIUM";2;"SPARKX-LOGO4";;;
27;"U$22,U$1";"GND1";2;"";;;
28;"JP1,JP5,JP6,JP2";"MICRO-FIDUCIAL";4;"FIDUCIALUFIDUCIAL";;;
29;"U$17";"PWR-()-03";1;"";;;
30;"J1";"MICRO-SD-SOCKET";1;"MICRO-SD";;;
31;"U$28,U$19";"#5";2;"";;;
32;"J6";"USB-MICROB-PTH-MILL";1;"";;;
33;"R11";"0603";1;"4.7k";;;
34;"C1";"0603";1;"10uF";;;
35;"U$40,U$16";"PHONES0";2;"";;;
36;"LOGO1";"OSHW-LOGO-MINI";1;"OSHW-LOGOMINI";;;
37;"JP10";"1X03_NO_SILK";1;"PTH";;;
38;"LOGO2";"OSHW-LOGO-MINI@1";1;"OSHW-LOGOMINI";;;
39;"JP12";"1X02_NO_SILK";1;"PTH";;;

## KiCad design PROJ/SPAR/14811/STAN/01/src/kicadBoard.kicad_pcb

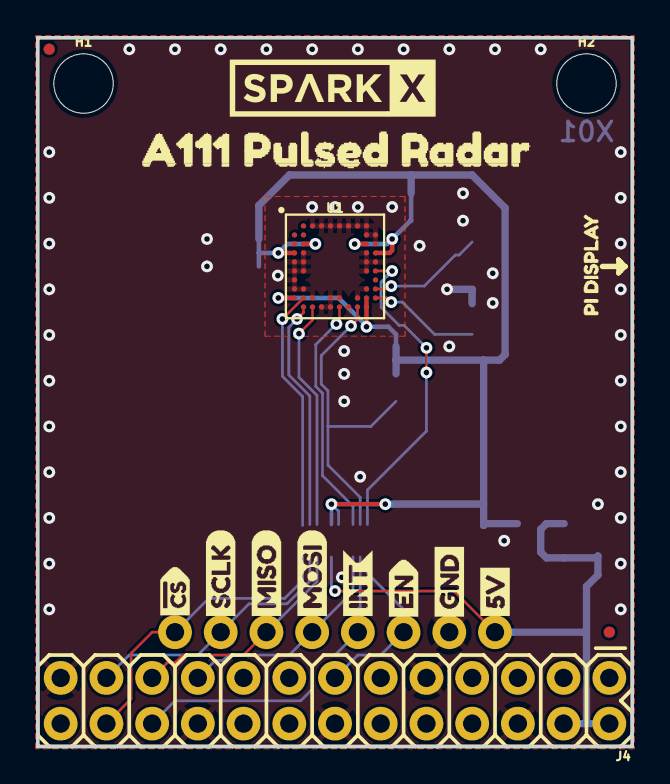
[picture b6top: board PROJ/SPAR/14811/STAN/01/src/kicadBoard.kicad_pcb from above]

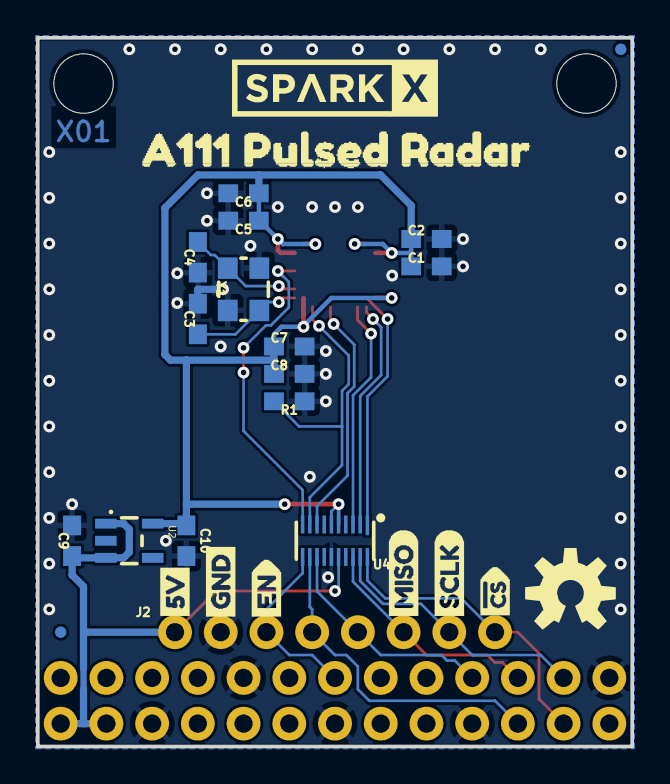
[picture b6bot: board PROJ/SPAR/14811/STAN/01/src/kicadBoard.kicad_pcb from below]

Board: 2 copper layers, 33.0 x 39.4 mm, 44 parts (26 on the bottom side), 17 nets.

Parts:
C1, C5, C7: 0.1uF; 0603
C2, C6, C8, C9, C10: 1.0uF; 0603
C3, C4: 10pF; 0603
FD1, FD2, FD3, FD4: FIDUCIALUFIDUCIAL; FIDUCIAL-MICRO
FRAME1: FRAME-LETTER; CREATIVE_COMMONS
H1, H2: STAND-OFF
J2: 1X08_NO_SILK
J4: RASPBERRYPI-26-PIN-GPIO; 2X13
LOGO1, LOGO3: SPARKX-LOGO5; SPARKX-LARGE
LOGO2: OSHW-LOGOM; OSHW-LOGO-M
R1: 100k; 0603
U1: A111
U2: V_REG_AP2112K-1.8; SOT23-5
U4: TXB0108DQSR; UFDFN-20
U$1, U$9: A111_PULSED_RADAR9
U$2, U$10: SCLK3
U$3, U$11: MISO4
U$4: MOSI5
U$5: INT8
U$6, U$18: EN9
U$7, U$15: GND0
U$8, U$16: 5V1
U$12: PI_DISPLAY9
U$13, U$17: #CS9
Y1: 26MHz; CRYSTAL-SMD-3.2X2.5MM

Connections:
1.8V: C1.1, C2.1, C5.1, C6.1, C7.1, C8.1, C10.1, U1.C2, U1.C9, U1.D1, U1.D10, U1.J1, U1.J9, U1.K9, U2.5, U4.5, U4.6
5V: C9.1, J2.1, J4.2, J4.4, U2.1, U2.3, U4.16
ENABLE: U1.F10, U4.10
ENABLE_RPI: J2.3, J4.13, U4.11
GND: C1.2, C2.2, C3.2, C4.1, C5.2, C6.2, C7.2, C8.2, C9.2, C10.2, J2.2, J4.6, J4.9, J4.14, J4.20, J4.25, R1.1, U1.A3, U1.A4, U1.A5, U1.A6, U1.A7, U1.A8, U1.A9, U1.B2, U1.B9, U1.B10, U1.C1, U1.C10, U1.D2, U1.D9, U1.E1, U1.E2, U1.E9, U1.E10, U1.F1, U1.F2, U1.F9, U1.G1, U1.G10, U1.H1, U1.H2, U1.H9, U1.J3, U1.J5, U1.J6, U1.J8, U1.K4, U1.K5, U1.K7, U4.15, Y1.2, Y1.4
INTERRUPT: R1.2, U1.K8, U4.9
INTERRUPT_RPI: J2.4, J4.22, U4.12
MISO: U1.K3, U4.3
MISO_RPI: J2.6, J4.21, U4.18
MOSI: U1.K6, U4.8
MOSI_RPI: J2.5, J4.19, U4.13
unnamed: C3.1, U1.J10, Y1.1
unnamed: C4.2, U1.H10, Y1.3
SCLK: U1.K2, U4.2
SCLK_RPI: J2.7, J4.23, U4.19
~CS: U1.J2, U4.1
~CS_RPI: J2.8, J4.24, U4.20

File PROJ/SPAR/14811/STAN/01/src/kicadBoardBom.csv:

"Id";"Designator";"Package";"Quantity";"Designation";"Supplier and ref";
1;"U$17,U$13";"#CS9";2;"";;;
2;"FRAME1";"CREATIVE_COMMONS";1;"FRAME-LETTER";;;
3;"U$3,U$11";"MISO4";2;"";;;
4;"FD1,FD2,FD4,FD3";"FIDUCIAL-MICRO";4;"FIDUCIALUFIDUCIAL";;;
5;"U$5";"INT8";1;"";;;
6;"U$4";"MOSI5";1;"";;;
7;"U1";"A111";1;"A111";;;
8;"U$2,U$10";"SCLK3";2;"";;;
9;"LOGO1,LOGO3";"SPARKX-LARGE";2;"SPARKX-LOGO5";;;
10;"U$8,U$16";"5V1";2;"";;;
11;"U$12";"PI_DISPLAY9";1;"";;;
12;"U$6,U$18";"EN9";2;"";;;
13;"H1,H2";"STAND-OFF";2;"STAND-OFF";;;
14;"J4";"2X13";1;"RASPBERRYPI-26-PIN-GPIO";;;
15;"U$1,U$9";"A111_PULSED_RADAR9";2;"";;;
16;"U$7,U$15";"GND0";2;"";;;
17;"C7,C1,C5";"0603";3;"0.1uF";;;
18;"C9,C8,C2,C6,C10";"0603";5;"1.0uF";;;
19;"C4,C3";"0603";2;"10pF";;;
20;"Y1";"CRYSTAL-SMD-3.2X2.5MM";1;"26MHz";;;
21;"J2";"1X08_NO_SILK";1;"";;;
22;"U4";"UFDFN-20";1;"TXB0108DQSR";;;
23;"LOGO2";"OSHW-LOGO-M";1;"OSHW-LOGOM";;;
24;"U2";"SOT23-5";1;"V_REG_AP2112K-1.8";;;
25;"R1";"0603";1;"100k";;;

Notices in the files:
parts and their libraries:
RELEASED UNDER THE CREATIVE COMMONS ATTRIBUTION SHARE-ALIKE 4.0 LICENSE
HTTPS://CREATIVECOMMONS.ORG/LICENSES/BY-SA/4.0
